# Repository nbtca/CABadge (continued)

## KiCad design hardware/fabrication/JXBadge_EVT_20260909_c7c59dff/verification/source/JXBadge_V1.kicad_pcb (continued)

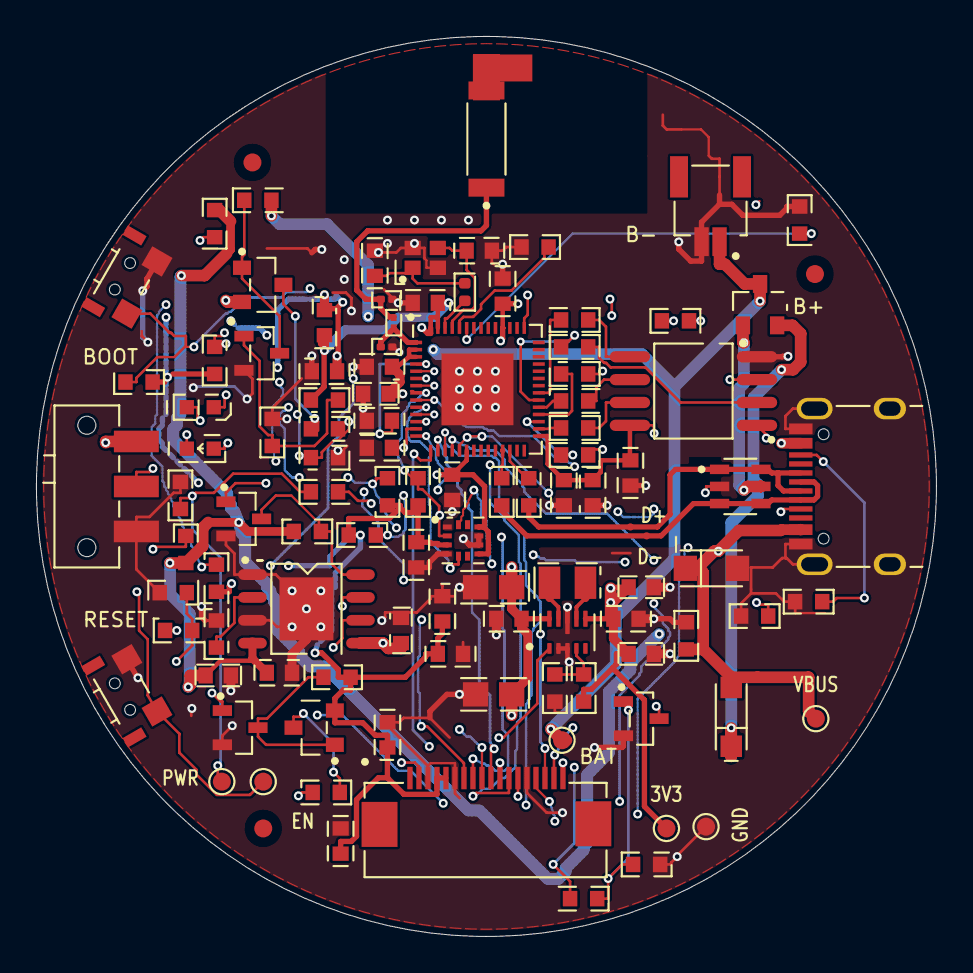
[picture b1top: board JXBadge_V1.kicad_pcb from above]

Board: 4 copper layers, 50.0 x 50.0 mm, 108 parts (0 on the bottom side), 68 nets.

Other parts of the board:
FID1, FID2, FID3: Fiducial; Fiducial_1mm_Mask2mm
